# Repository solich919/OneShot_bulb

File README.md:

# Sun bulb
This is my project of "The Sun" inspired by OneShot game. This is a DIY lamp/prop. Work-in-progress

# TODOs
- [x] Create a preliminary physical design
- [x] Develop LED driver circuit
- [ ] Develop control circuit <- *currently here*
- [ ] TBD
## Planned features
* Around 4W of output power
* Battery or/and USB powered
* USB-C connector (and/or induction charging, maybe)
* Adjustable brightness
* Touch or wireless controls (BT or control through web interface)
* 3D printed construction
* Smart functions

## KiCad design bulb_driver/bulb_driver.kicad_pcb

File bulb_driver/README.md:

# LM3410 led driver
The contents of this folder hold KiCad project files for LM3410 led driver prototype.
The main problem associated with the project is to generate ~22V from a Li-on cell and hold constant current at around 200 mA to drive the LED filament.
LM3410 from TI fits these requirements. A prototype was made to test the validity of this design.

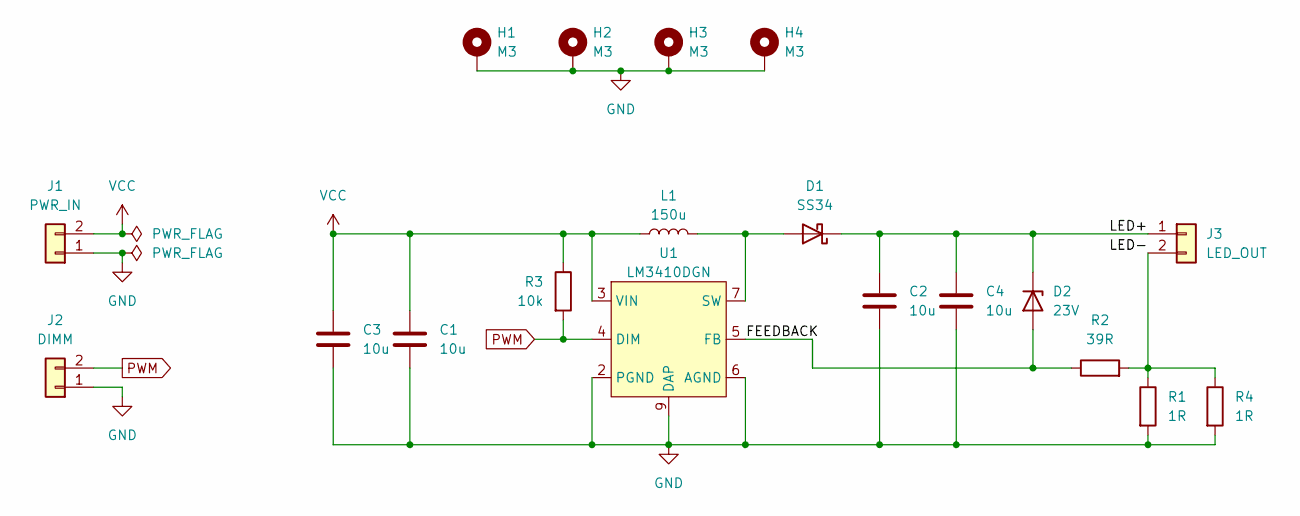
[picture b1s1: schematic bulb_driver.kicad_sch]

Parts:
C1, C2, C3, C4: 10u; C_1210_3225Metric
D1: SS34; D_SMC
D2: 23V; D_SOD-123
H1, H2, H3, H4: M3; MountingHole_3.2mm_M3_Pad_Via
J1: PWR_IN; SolderWire-1sqmm_1x02_P7.8mm_D1.4mm_OD3.9mm
J2: DIMM; PinHeader_1x02_P2.54mm_Vertical
J3: LED_OUT; SolderWire-1sqmm_1x02_P7.8mm_D1.4mm_OD3.9mm
L1: 150u; L_Bourns_SRR1210A
R1, R4: 1R; R_0805_2012Metric
R2: 39R; R_0805_2012Metric
R3: 10k; R_0805_2012Metric
U1: LM3410DGN; HVSSOP-8-1EP_3x3mm_P0.65mm_EP1.57x1.89mm

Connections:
/FEEDBACK: D2.2 (A), R2.1, U1.5 (FB)
/LED+: C2.1, C4.1, D1.1 (K), D2.1 (K), J3.1
/LED-: J3.2, R1.1, R2.2, R4.1
GND: C1.2, C2.2, C3.2, C4.2, H1.1, H2.1, H3.1, H4.1, J1.1, J2.1, R1.2, R4.2, U1.2 (PGND), U1.6 (AGND), U1.9 (DAP)
unnamed: D1.2 (A), L1.2, U1.7 (SW)
PWM: J2.2, R3.2, U1.4 (DIM)
VCC: C1.1, C3.1, J1.2, L1.1, R3.1, U1.3 (VIN)

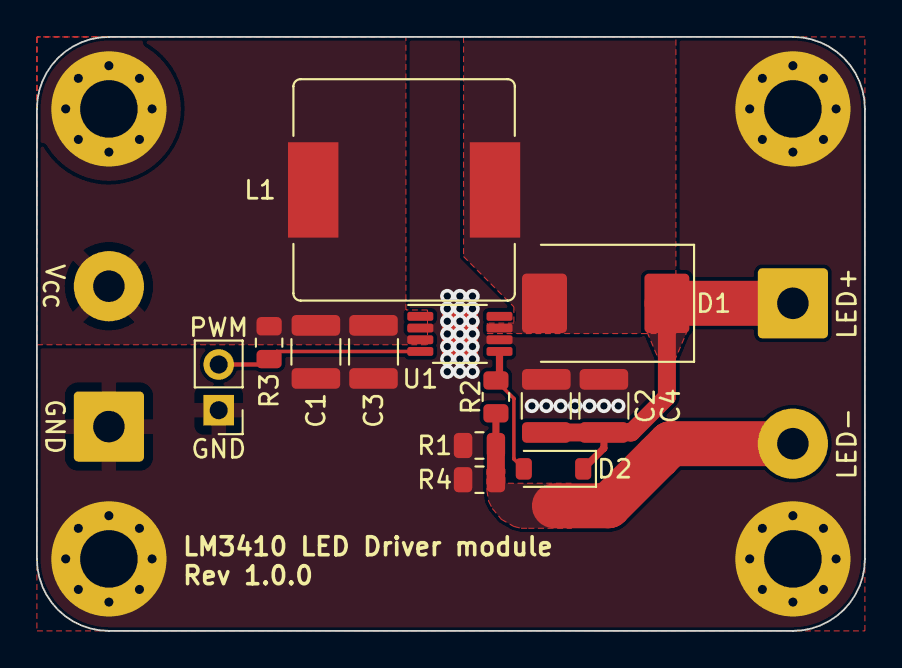
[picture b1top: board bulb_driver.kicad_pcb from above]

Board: 2 copper layers, 46.0 x 33.0 mm, 19 parts (0 on the bottom side), 7 nets.

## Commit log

2023-06-16 initial commit of led driver project
2023-06-16 Update README.md
    lm3410 max Vcc is 5,5V, so implementing USB-PD won't bring much benefit
2023-07-10 Update schematic
2023-07-17 Project update
2023-07-19 Generate production files and project update
2023-07-19 Add .gitignore
2023-07-19 Create target design schematic structure
2023-07-19 Cleanup libs
2023-07-19 Cleanup after merge
2023-07-19 Project update
    Add USB and Touch sheets
    Make initial schematic for uC block
2024-08-21 Create README.md for bulb_driver
2024-08-21 Update README.md
    Change project name and desc
2024-09-02 Update BMS schematic
    Add protection IC
2024-09-02 Update LED driver schematic
2024-09-02 Update KiCad project files
2024-09-02 Rename BMS schematic to battery
2024-09-02 Update schematics
2024-09-03 Add info text
